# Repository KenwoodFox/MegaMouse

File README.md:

# MegaMouse
MegaMouse! An atmega 328p powered micromouse!

# Getting Started

First, begin by cloning this repo and relevant submodules

```shell
git clone --recurse-submodules https://github.com/KenwoodFox/MegaMouse.git
```

Find hardware, software and docs in the directories below!

```
.
├── CAD                   # CAD and 3D models
├── Firmware              # Firmware and on-board code
├── Hardware              # Hardware and design files
│   └── MegaMouse         # PCB Design Files
│       └── Libraries     # KiCAD libraries
└── Static                # Static files
```

# Tag Naming System

```
v1.3
││ │
││ └─ Intermediete revision (reivew, software, minor change)
│└─── Major revision (hardware change, incompatable modification)
└──── Releasable Version
```

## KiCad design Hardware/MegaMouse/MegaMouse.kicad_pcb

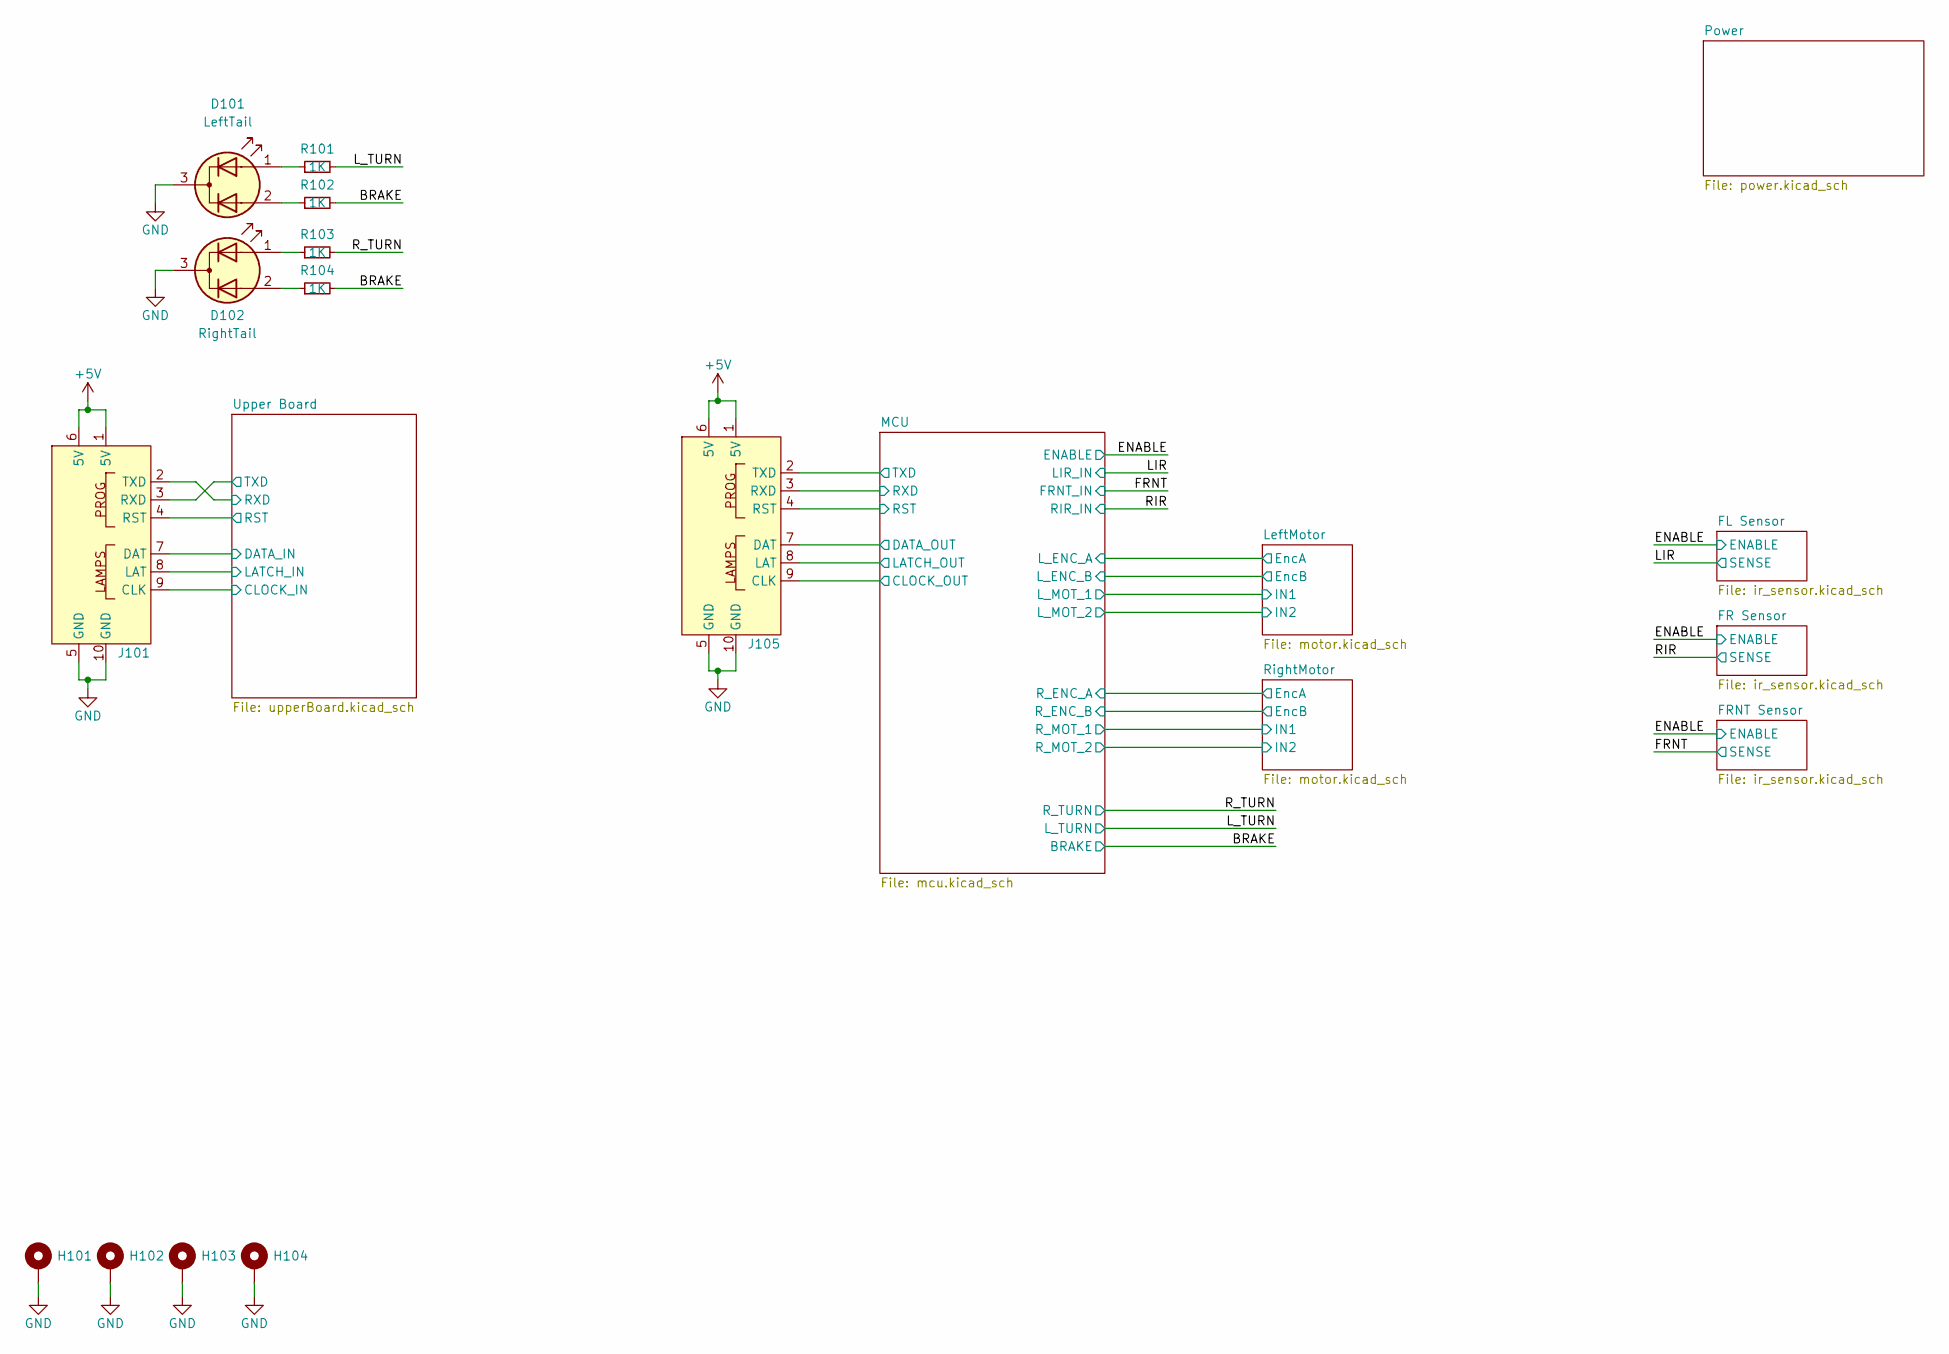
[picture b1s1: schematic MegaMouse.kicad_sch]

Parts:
D101: LeftTail; BrakeLight
D102: RightTail; BrakeLight
H101, H102, H103, H104: MountingHole_Pad; MountingHole_3mm_Pad
J101, J105: MegaInterconnect
R101, R102, R103, R104: 1K; R_0805_2012Metric

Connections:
+5V: J101.1 (5V), J101.6 (5V), J105.1 (5V), J105.6 (5V); also elsewhere on the board
/BRAKE: R102.2, R104.2; also elsewhere on the board
/L_TURN: R101.2; also elsewhere on the board
/MCU/CLOCK: J105.9 (CLK); also elsewhere on the board
/MCU/DATA_OUT: J105.7 (DAT); also elsewhere on the board
/MCU/LATCH: J105.8 (LAT); also elsewhere on the board
/MCU/RST: J105.4 (RST); also elsewhere on the board
/MCU/RXD: J105.3 (RXD); also elsewhere on the board
/MCU/TXD: J105.2 (TXD); also elsewhere on the board
/R_TURN: R103.2; also elsewhere on the board
/Upper Board/CLOCK_IN: J101.9 (CLK); also elsewhere on the board
/Upper Board/DATA_IN: J101.7 (DAT); also elsewhere on the board
/Upper Board/LATCH_IN: J101.8 (LAT); also elsewhere on the board
/Upper Board/RST: J101.4 (RST); also elsewhere on the board
/Upper Board/RXD: J101.2 (TXD); also elsewhere on the board
/Upper Board/TXD: J101.3 (RXD); also elsewhere on the board
GND: D101.3 (K), D102.3 (K), H101.1, H102.1, H103.1, H104.1, J101.5 (GND), J101.10 (GND), J105.5 (GND), J105.10 (GND); also elsewhere on the board
unnamed: D101.1 (A1), R101.1
unnamed: D101.2 (A2), R102.1
unnamed: D102.1 (A1), R103.1
unnamed: D102.2 (A2), R104.1

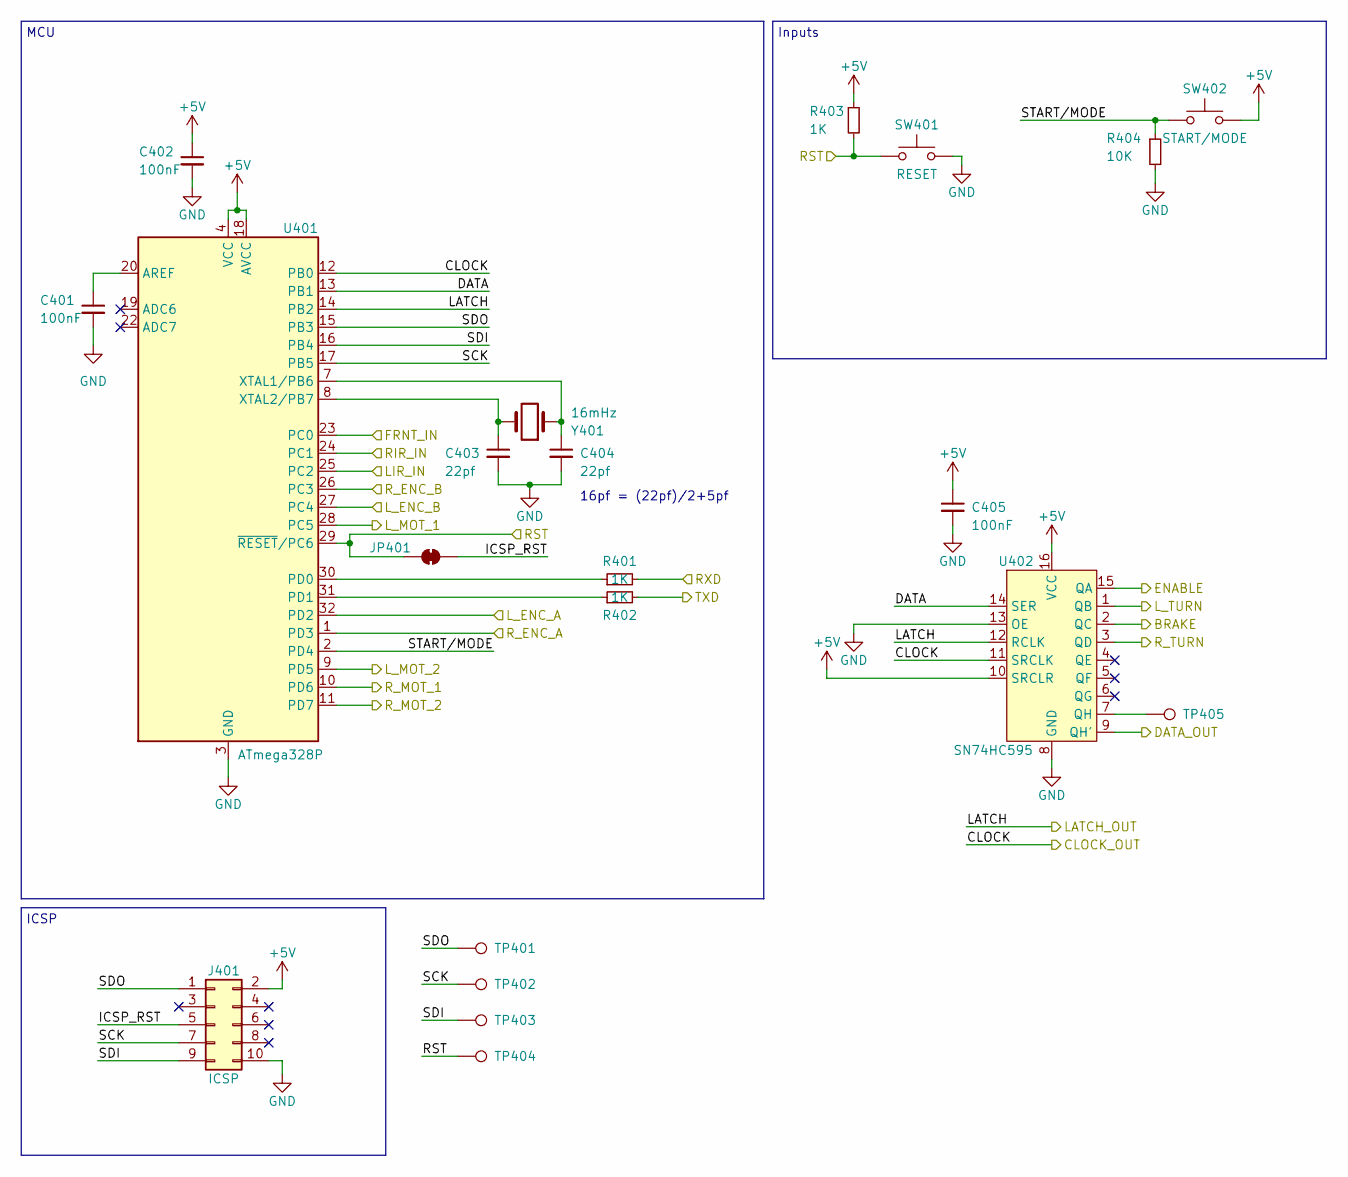
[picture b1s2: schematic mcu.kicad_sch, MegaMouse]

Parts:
C401, C402, C405: 100nF; C_0805_2012Metric
C403, C404: 22pf; C_0603_1608Metric
J401: ICSP; Tag-Connect_TC2050-IDC-FP_2x05_P1.27mm_Vertical
JP401: RSTBridge; SolderJumper-2_P1.3mm_Bridged_Pad1.0x1.5mm
R401, R402, R403: 1K; R_0805_2012Metric
R404: 10K; R_0805_2012Metric
SW401: RESET; SW_PUSH_6mm_H5mm
SW402: START/MODE; SW_Tactile_SKHH_Angled; LCSC# C384611
TP401, TP402, TP403, TP404, TP405: TestPoint; TestPoint_Pad_2.0x2.0mm
U401: ATmega328P; TQFP-32_7x7mm_P0.8mm
U402: SN74HC595
Y401: 16mHz; Crystal_SMD_HC49-SD

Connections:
+5V: C402.1, C405.1, J401.2, R403.1, SW402.2, U401.4 (VCC), U401.6 (VCC), U401.18 (AVCC), U402.10 (SRCLR), U402.16 (VCC); also elsewhere on the board
/BRAKE: U402.2 (QC); also elsewhere on the board
/ENABLE: U402.15 (QA); also elsewhere on the board
/FRNT: U401.23 (PC0); also elsewhere on the board
/LIR: U401.25 (PC2); also elsewhere on the board
/L_TURN: U402.1 (QB); also elsewhere on the board
/LeftMotor/EncA: U401.32 (PD2); also elsewhere on the board
/LeftMotor/EncB: U401.27 (PC4); also elsewhere on the board
/LeftMotor/IN1: U401.28 (PC5); also elsewhere on the board
/LeftMotor/IN2: U401.9 (PD5); also elsewhere on the board
/MCU/CLOCK: U401.12 (PB0), U402.11 (SRCLK); also elsewhere on the board
/MCU/DATA: U401.13 (PB1), U402.14 (SER)
/MCU/DATA_OUT: U402.9 (QH'); also elsewhere on the board
/MCU/ICSP_RST: J401.5, JP401.2 (B)
/MCU/LATCH: U401.14 (PB2), U402.12 (RCLK); also elsewhere on the board
/MCU/RST: JP401.1 (A), R403.2, SW401.1, TP404.1, U401.29 (~RESET/PC6); also elsewhere on the board
/MCU/RXD: R401.2; also elsewhere on the board
/MCU/R_ENC_A: U401.1 (PD3); also elsewhere on the board
/MCU/R_ENC_B: U401.26 (PC3); also elsewhere on the board
/MCU/R_MOT_1: U401.10 (PD6); also elsewhere on the board
/MCU/R_MOT_2: U401.11 (PD7); also elsewhere on the board
/MCU/SCK: J401.7, TP402.1, U401.17 (PB5)
/MCU/SDI: J401.9, TP403.1, U401.16 (PB4)
/MCU/SDO: J401.1, TP401.1, U401.15 (PB3)
/MCU/START/MODE: R404.1, SW402.1, U401.2 (PD4)
/MCU/TXD: R402.2; also elsewhere on the board
/RIR: U401.24 (PC1); also elsewhere on the board
/R_TURN: U402.3 (QD); also elsewhere on the board
GND: C401.2, C402.2, C403.2, C404.2, C405.2, J401.10, R404.2, SW401.2, U401.3 (GND), U401.5 (GND), U401.21 (GND), U402.8 (GND), U402.13 (OE); also elsewhere on the board
unnamed: C401.1, U401.20 (AREF)
unnamed: R401.1, U401.30 (PD0)
unnamed: R402.1, U401.31 (PD1)
unnamed: C404.1, U401.7 (XTAL1/PB6), Y401.1
unnamed: C403.1, U401.8 (XTAL2/PB7), Y401.2
unnamed: TP405.1, U402.7 (QH)

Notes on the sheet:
ICSP
MCU
Inputs
16pf = (22pf)/2+5pf

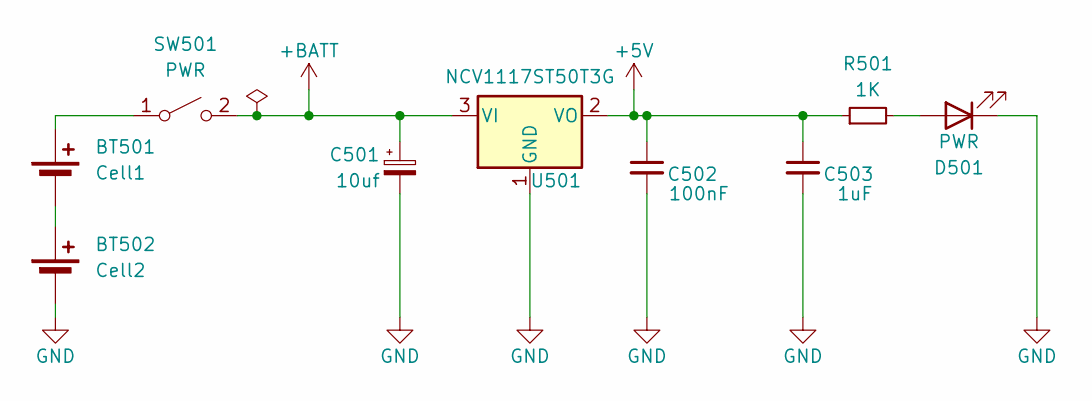
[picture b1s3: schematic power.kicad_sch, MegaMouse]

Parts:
BT501: Cell1; BatteryHolder_MPD_BH-18650-PC2; LCSC# C5290176
BT502: Cell2; BatteryHolder_MPD_BH-18650-PC2; LCSC# C5290176
C501: 10uf; CP_Elec_4x3
C502: 100nF; C_0805_2012Metric
C503: 1uF; C_0805_2012Metric
D501: PWR; LED_0805_2012Metric
R501: 1K; R_0805_2012Metric
SW501: PWR; EG1218; LCSC# C273394
U501: NCV1117ST50T3G; SOT-223

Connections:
+5V: C502.1, C503.1, R501.1, U501.2 (VO); also elsewhere on the board
+BATT: C501.1, SW501.2 (B), U501.3 (VI); also elsewhere on the board
GND: BT502.2 (-), C501.2, C502.2, C503.2, D501.1 (K), U501.1 (GND); also elsewhere on the board
unnamed: BT501.1 (+), SW501.1 (A)
unnamed: BT501.2 (-), BT502.1 (+)
unnamed: D501.2 (A), R501.2

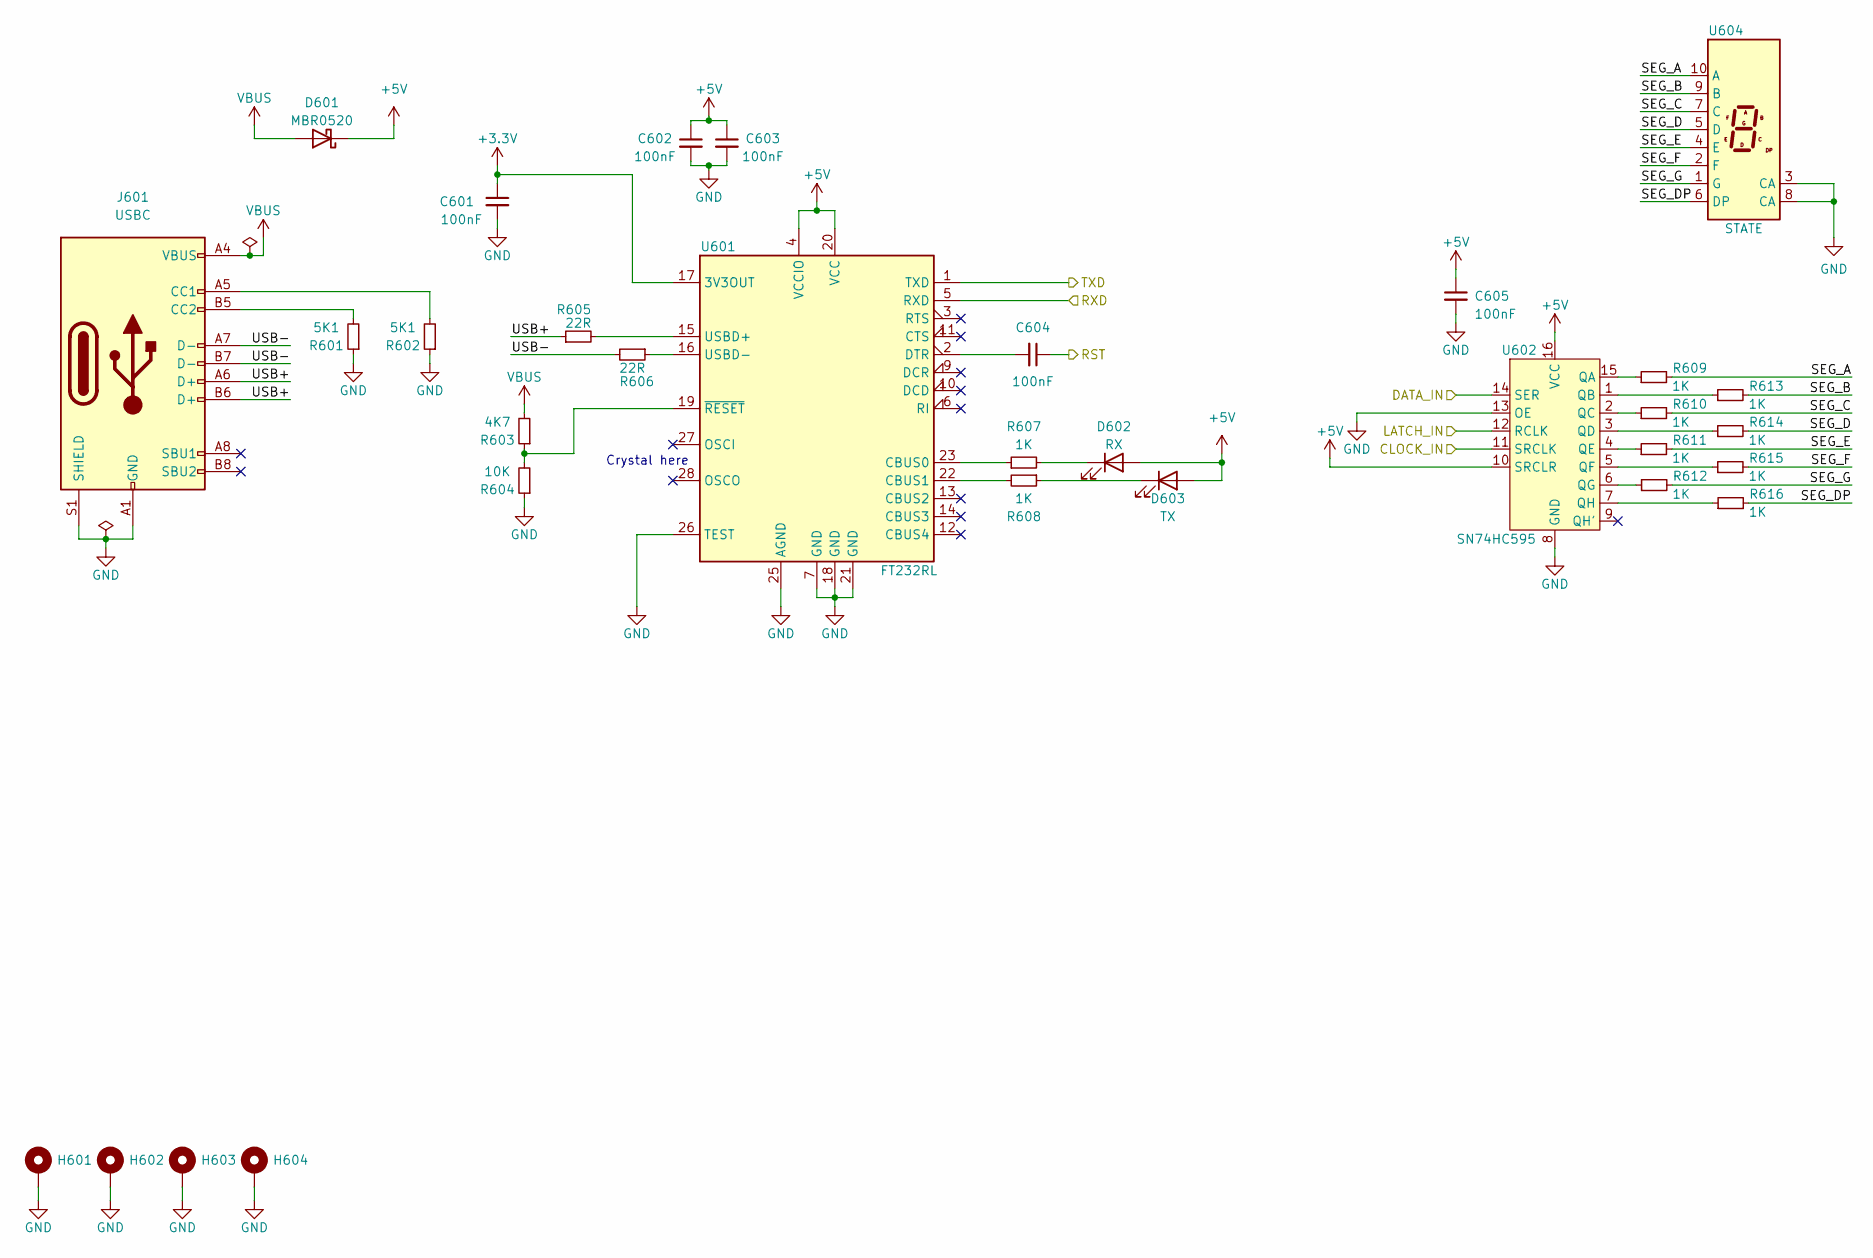
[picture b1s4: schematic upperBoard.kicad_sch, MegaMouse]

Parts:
C601, C602, C603, C604, C605: 100nF; C_0805_2012Metric
D601: MBR0520; D_SOD-123
D602: RX; LED_0805_2012Metric
D603: TX; LED_0805_2012Metric
H601, H602, H603, H604: MountingHole_Pad; MountingHole_3mm_Pad
J601: USBC; USB_C_Receptacle_XKB_U262-16XN-4BVC11
R601, R602: 5K1; R_0805_2012Metric
R603: 4K7; R_0805_2012Metric
R604: 10K; R_0805_2012Metric
R605, R606: 22R; R_0805_2012Metric
R607, R608, R609, R610, R611, R612, R613, R614, R615, R616: 1K; R_0805_2012Metric
U601: FT232RL; SSOP-28_5.3x10.2mm_P0.65mm; LCSC# C8690
U602: SN74HC595
U604: STATE; SM420391N8

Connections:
+3.3V: C601.1, U601.17 (3V3OUT)
+5V: C602.1, C603.1, C605.1, D601.1 (K), D602.2 (A), D603.2 (A), U601.4 (VCCIO), U601.20 (VCC), U602.10 (SRCLR), U602.16 (VCC); also elsewhere on the board
/Upper Board/CLOCK_IN: U602.11 (SRCLK); also elsewhere on the board
/Upper Board/DATA_IN: U602.14 (SER); also elsewhere on the board
/Upper Board/LATCH_IN: U602.12 (RCLK); also elsewhere on the board
/Upper Board/RST: C604.1; also elsewhere on the board
/Upper Board/RXD: U601.5 (RXD); also elsewhere on the board
/Upper Board/SEG_A: R609.2, U604.10 (A)
/Upper Board/SEG_B: R613.2, U604.9 (B)
/Upper Board/SEG_C: R610.2, U604.7 (C)
/Upper Board/SEG_D: R614.2, U604.5 (D)
/Upper Board/SEG_DP: R616.2, U604.6 (DP)
/Upper Board/SEG_E: R611.2, U604.4 (E)
/Upper Board/SEG_F: R615.2, U604.2 (F)
/Upper Board/SEG_G: R612.2, U604.1 (G)
/Upper Board/TXD: U601.1 (TXD); also elsewhere on the board
/Upper Board/USB+: J601.A6 (D+), J601.B6 (D+), R605.1
/Upper Board/USB-: J601.A7 (D-), J601.B7 (D-), R606.2
GND: C601.2, C602.2, C603.2, C605.2, H601.1, H602.1, H603.1, H604.1, J601.A1 (GND), J601.A12 (GND), J601.B1 (GND), J601.B12 (GND), J601.S1 (SHIELD), R601.1, R602.1, R604.1, U601.7 (GND), U601.18 (GND), U601.21 (GND), U601.25 (AGND), U601.26 (TEST), U602.8 (GND), U602.13 (OE), U604.3 (CA), U604.8 (CA); also elsewhere on the board
unnamed: D602.1 (K), R607.2
unnamed: D603.1 (K), R608.1
unnamed: J601.A5 (CC1), R602.2
unnamed: J601.B5 (CC2), R601.2
unnamed: R607.1, U601.23 (CBUS0)
unnamed: R608.2, U601.22 (CBUS1)
unnamed: C604.2, U601.2 (DTR)
unnamed: R605.2, U601.15 (USBD+)
unnamed: R606.1, U601.16 (USBD-)
unnamed: R603.1, R604.2, U601.19 (~RESET)
unnamed: R609.1, U602.15 (QA)
unnamed: R613.1, U602.1 (QB)
unnamed: R610.1, U602.2 (QC)
unnamed: R614.1, U602.3 (QD)
unnamed: R611.1, U602.4 (QE)
unnamed: R615.1, U602.5 (QF)
unnamed: R612.1, U602.6 (QG)
unnamed: R616.1, U602.7 (QH)
VBUS: D601.2 (A), J601.A4 (VBUS), J601.A9 (VBUS), J601.B4 (VBUS), J601.B9 (VBUS), R603.2

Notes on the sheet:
Crystal here

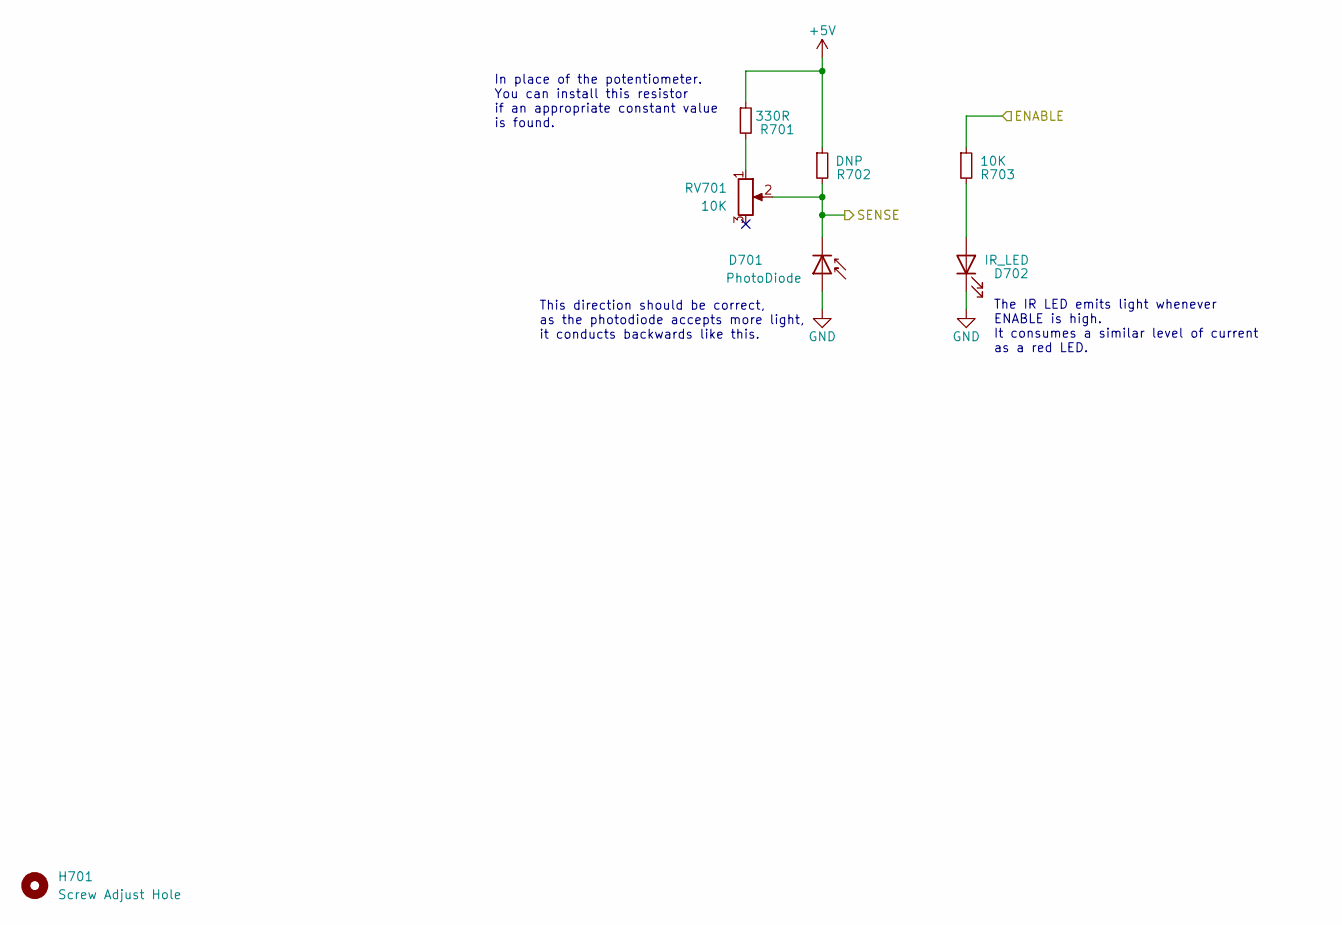
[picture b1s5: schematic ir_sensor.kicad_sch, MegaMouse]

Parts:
D701: PhotoDiode; LED_D5.0mm_Horizontal_O1.27mm_Z3.0mm_IRBlack
D702: IR_LED; LED_D5.0mm_Horizontal_O1.27mm_Z3.0mm_Clear
H701: Screw Adjust Hole; MountingHole_3mm
R701: 330R; R_0805_2012Metric
R702: DNP; R_0805_2012Metric
R703: 10K; R_0805_2012Metric
RV701: 10K; Potentiometer_Bourns_TC33X_Vertical

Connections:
+5V: R701.1, R702.1; also elsewhere on the board
/ENABLE: R703.1; also elsewhere on the board
/LIR: D701.1 (K), R702.2, RV701.2; also elsewhere on the board
GND: D701.2 (A), D702.1 (K); also elsewhere on the board
unnamed: D702.2 (A), R703.2
unnamed: R701.2, RV701.1

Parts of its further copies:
D801, D901: PhotoDiode; LED_D5.0mm_Horizontal_O1.27mm_Z3.0mm_IRBlack
D802, D902: IR_LED; LED_D5.0mm_Horizontal_O1.27mm_Z3.0mm_Clear
H801, H901: Screw Adjust Hole; MountingHole_3mm
R801, R901: 330R; R_0805_2012Metric
R802, R902: DNP; R_0805_2012Metric
R803, R903: 10K; R_0805_2012Metric
RV801, RV901: 10K; Potentiometer_Bourns_TC33X_Vertical

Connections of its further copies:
+5V: R801.1, R802.1, R901.1, R902.1; also elsewhere on the board
/ENABLE: R803.1, R903.1; also elsewhere on the board
/FRNT: D901.1 (K), R902.2, RV901.2; also elsewhere on the board
/RIR: D801.1 (K), R802.2, RV801.2; also elsewhere on the board
GND: D801.2 (A), D802.1 (K), D901.2 (A), D902.1 (K); also elsewhere on the board
unnamed: D802.2 (A), R803.2
unnamed: D902.2 (A), R903.2
unnamed: R801.2, RV801.1
unnamed: R901.2, RV901.1

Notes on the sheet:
This direction should be correct, as the photodiode accepts more light, it conducts backwards like this.
The IR LED emits light whenever ENABLE is high. It consumes a similar level of current as a red LED.
In place of the potentiometer. You can install this resistor if an appropriate constant value is found.

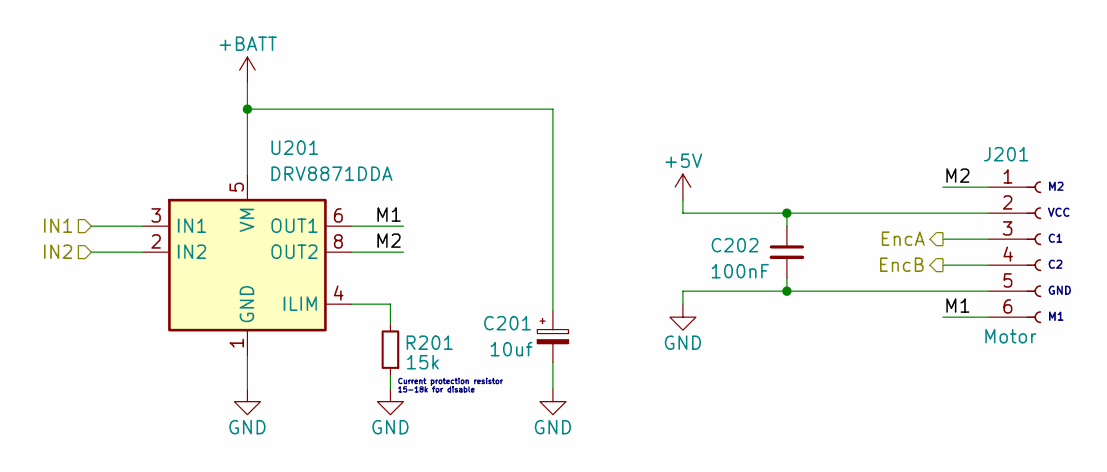
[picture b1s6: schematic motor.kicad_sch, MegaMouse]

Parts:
C201: 10uf; CP_Elec_4x3
C202: 100nF; C_0805_2012Metric
J201: Motor; MicroMotor
R201: 15k; R_0805_2012Metric
U201: DRV8871DDA; Texas_HTSOP-8-1EP_3.9x4.9mm_P1.27mm_EP2.95x4.9mm_Mask2.4x3.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

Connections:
+5V: C202.1, J201.2; also elsewhere on the board
+BATT: C201.1, U201.5 (VM); also elsewhere on the board
/LeftMotor/EncA: J201.3; also elsewhere on the board
/LeftMotor/EncB: J201.4; also elsewhere on the board
/LeftMotor/IN1: U201.3 (IN1); also elsewhere on the board
/LeftMotor/IN2: U201.2 (IN2); also elsewhere on the board
/LeftMotor/M1: J201.6, U201.6 (OUT1)
/LeftMotor/M2: J201.1, U201.8 (OUT2)
GND: C201.2, C202.2, J201.5, R201.1, U201.1 (GND), U201.7 (GND), U201.9 (GND); also elsewhere on the board
unnamed: R201.2, U201.4 (ILIM)

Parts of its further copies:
C301: 10uf; CP_Elec_4x3
C302: 100nF; C_0805_2012Metric
J301: Motor; MicroMotor
R301: 15k; R_0805_2012Metric
U301: DRV8871DDA; Texas_HTSOP-8-1EP_3.9x4.9mm_P1.27mm_EP2.95x4.9mm_Mask2.4x3.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

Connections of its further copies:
+5V: C302.1, J301.2; also elsewhere on the board
+BATT: C301.1, U301.5 (VM); also elsewhere on the board
/MCU/R_ENC_A: J301.3; also elsewhere on the board
/MCU/R_ENC_B: J301.4; also elsewhere on the board
/MCU/R_MOT_1: U301.3 (IN1); also elsewhere on the board
/MCU/R_MOT_2: U301.2 (IN2); also elsewhere on the board
/RightMotor/M1: J301.6, U301.6 (OUT1)
/RightMotor/M2: J301.1, U301.8 (OUT2)
GND: C301.2, C302.2, J301.5, R301.1, U301.1 (GND), U301.7 (GND), U301.9 (GND); also elsewhere on the board
unnamed: R301.2, U301.4 (ILIM)

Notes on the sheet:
GND
Current protection resistor 15-18k for disable
VCC

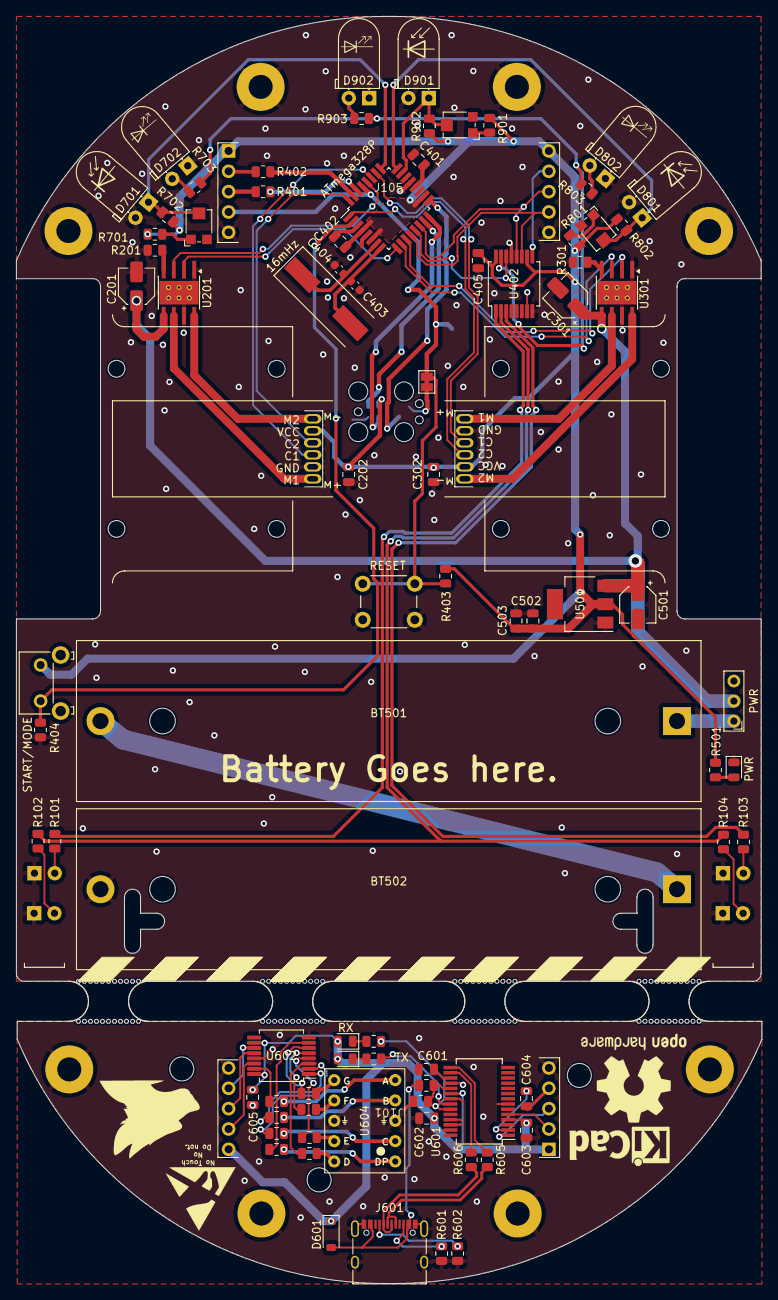
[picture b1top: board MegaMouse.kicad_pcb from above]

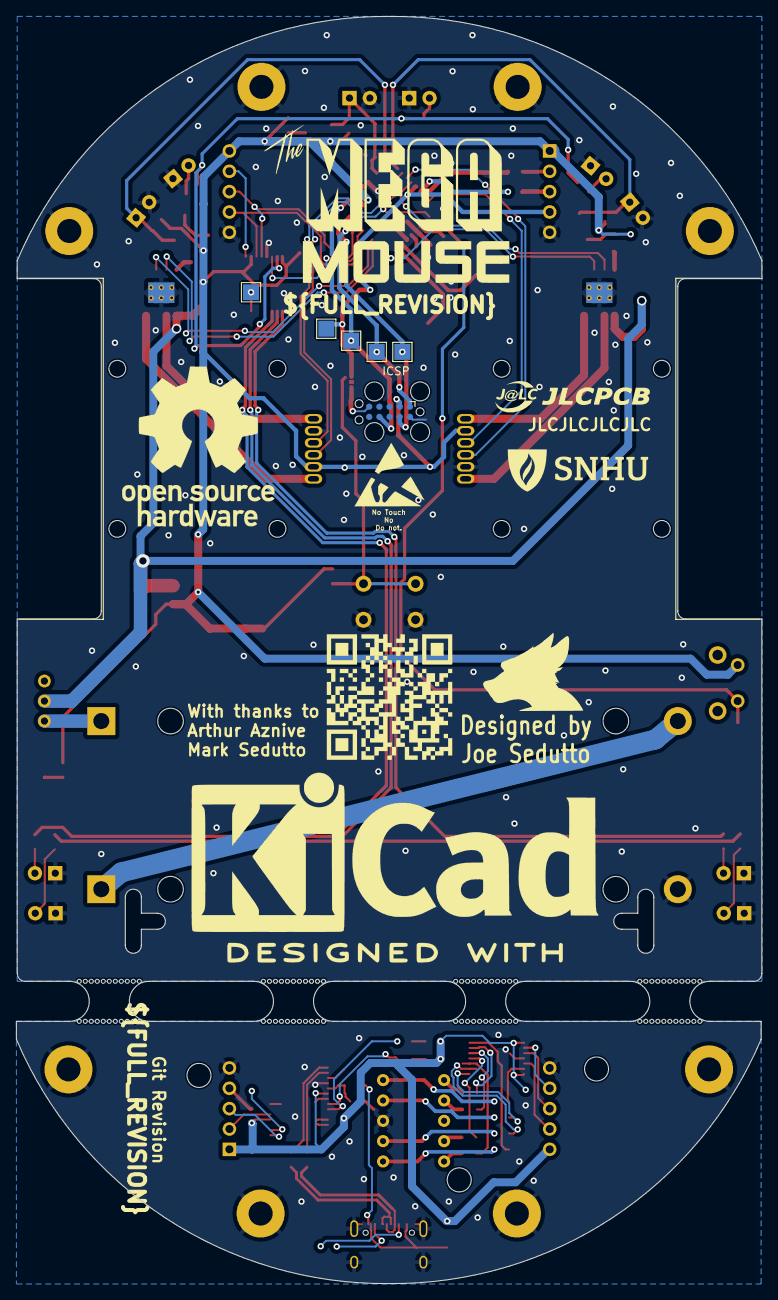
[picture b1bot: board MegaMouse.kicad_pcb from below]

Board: 2 copper layers, 93.1 x 158.2 mm, 119 parts (7 on the bottom side), 91 nets.

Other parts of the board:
SNHU_NEW***: LOGO; SNHU_NEW
Stripes: Stripes
Stripes#2, Stripes#3, Stripes#4, Stripes#5, Stripes#6, Stripes#7, Stripes#8, Stripes#9: Stripes
mouse-bite-5mm-slot, mouse-bite-5mm-slot#2, mouse-bite-5mm-slot#3, mouse-bite-5mm-slot#4: VAL**; mouse-bite-5mm-slot

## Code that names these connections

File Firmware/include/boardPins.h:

#include <Arduino.h>

#ifndef _BOARD_PINS_H
#define _BOARD_PINS_H

// Encoders
#define LENCA 2  // PD2
#define LENCB A4 // PC4
#define RENCA 3  // PD3
#define RENCB A3 // PC3

// Motors
#define LMOT1 A5 // PC5
#define LMOT2 5  // PD5

// Shift Pins
#define DIN_PIN 9
#define CLK_PIN 8
#define LAT_PIN 10

#endif

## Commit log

2023-03-01 Create 3d model for motors
2023-03-01 Brake lights!
2023-03-02 Bump libs
2023-03-02 Add brakelight as full kicad_mod
2023-03-03 Make awesome
2023-03-06 Clean board
2023-03-20 Add second layer
2023-03-20 Add panelization
2023-03-20 move upper body
2023-03-23 Throw on second layer and target a v1.0
2023-03-24 Boilerplate firmware
2023-03-24 Bump all
2023-03-24 remove missing dep
2023-03-24 Dont bump firmware in discord
2023-03-24 Bump kibot
2023-03-24 Even more stuff! also bump libs
2023-03-25 Add kibot config
2023-03-25 Remove inaccesable datasheet
2023-03-25 Bump config
2023-03-27 There should be no mention of any datasheet for that diodeg
2023-03-27 Bump verbose
2023-03-27 remove verbose
2023-03-27 Add silk
2023-03-27 Bump workflow
2023-03-27 Awesomeness
2023-03-27 Add decoupling caps and 3d models
2023-03-27 Fix crystal
2023-03-27 Add more wiring
2023-03-28 Add IR sensor
2023-03-28 Add silkscreen!
2023-03-28 Add inital photodiodes
2023-03-28 Add in some more, random junk
2023-03-29 Add lines for enabling emittersg
2023-03-29 Remove LCSC to fix builds
2023-03-29 Fix DRC and prep for a v1.0 release!
2023-03-29 Bump kenwoodfox libs
2023-03-29 fixup! Bump kenwoodfox libs
2023-03-29 Prepare for prototype
2023-03-29 Ad slots for feet
2023-03-29 Bump readme
2023-03-30 Comments
2023-03-30 Bump embedded 3d
2023-03-30 Carlstrom Review (#2)
    Thank you to Professor Carlstrom for reviewing!
2023-03-31 Add recomendations from ka2qfx
2023-04-04 Bump to kicad7
2023-04-05 fixup! Bump to kicad7
2023-04-05 Add USBC 3d Model back in
2023-04-05 Confirm encoder
2023-04-06 Clean brd
2023-04-14 Redo segment
2023-06-13 Add stencil dimensions
2023-06-27 Create bridge component
2023-06-29 Add mounting holes into bridge
2023-06-29 Bump bridge again
2023-08-28 Bump pcb design
2023-10-10 Add stencil
2023-10-10 Include docs from upstream
2023-10-10 add workflows from upstream template
2023-10-10 Bump all images
2023-10-12 Add simulator
2023-10-12 Create cross-compile algorithm
2023-10-12 Algorithm can mark and show data
2023-10-12 Code runs but does not score on maze.
    Need to consider using the tile struct or not
    need methods for setting left and right
2023-10-12 Make code portable
2023-10-12 tidy some more and consider methods for more efficent data storage
2023-10-12 Alg can record number of steps (precusor to flood fill/anti-step
2023-10-12 Boilerplate target system
2023-10-12 Closeup
2023-10-16 Mouse now relies on upstream lib
2023-10-19 Bump PCB and BOM
2023-10-19 Clean up battery trace width
2023-10-23 Add BOM
2023-11-02 Ignore binary files
2023-11-02 Add methods to update absolute wall positions
2023-11-02 Rotate method allows bot to convert relative readings into map readings
2023-11-02 Seperate env (and make space for future ports)
2023-11-05 Add LCSC part number
2023-11-06 Include changes from upstream
2023-11-14 add intended direction solvoing
2023-11-23 fix pins and blinkers
2024-09-23 Bump to new k8 format for config
2024-09-23 Bump upload actions to v4
2024-09-23 Fix ERC
2024-09-23 Bump outdated
2024-10-03 Fix DRC Errors
2025-12-03 Fix a longstanding bug with tx/rx mismatch (use single footprint now)
2025-12-04 Bump CI
2025-12-04 Verification 1 (#3)
    And thats all we have time for folks.
